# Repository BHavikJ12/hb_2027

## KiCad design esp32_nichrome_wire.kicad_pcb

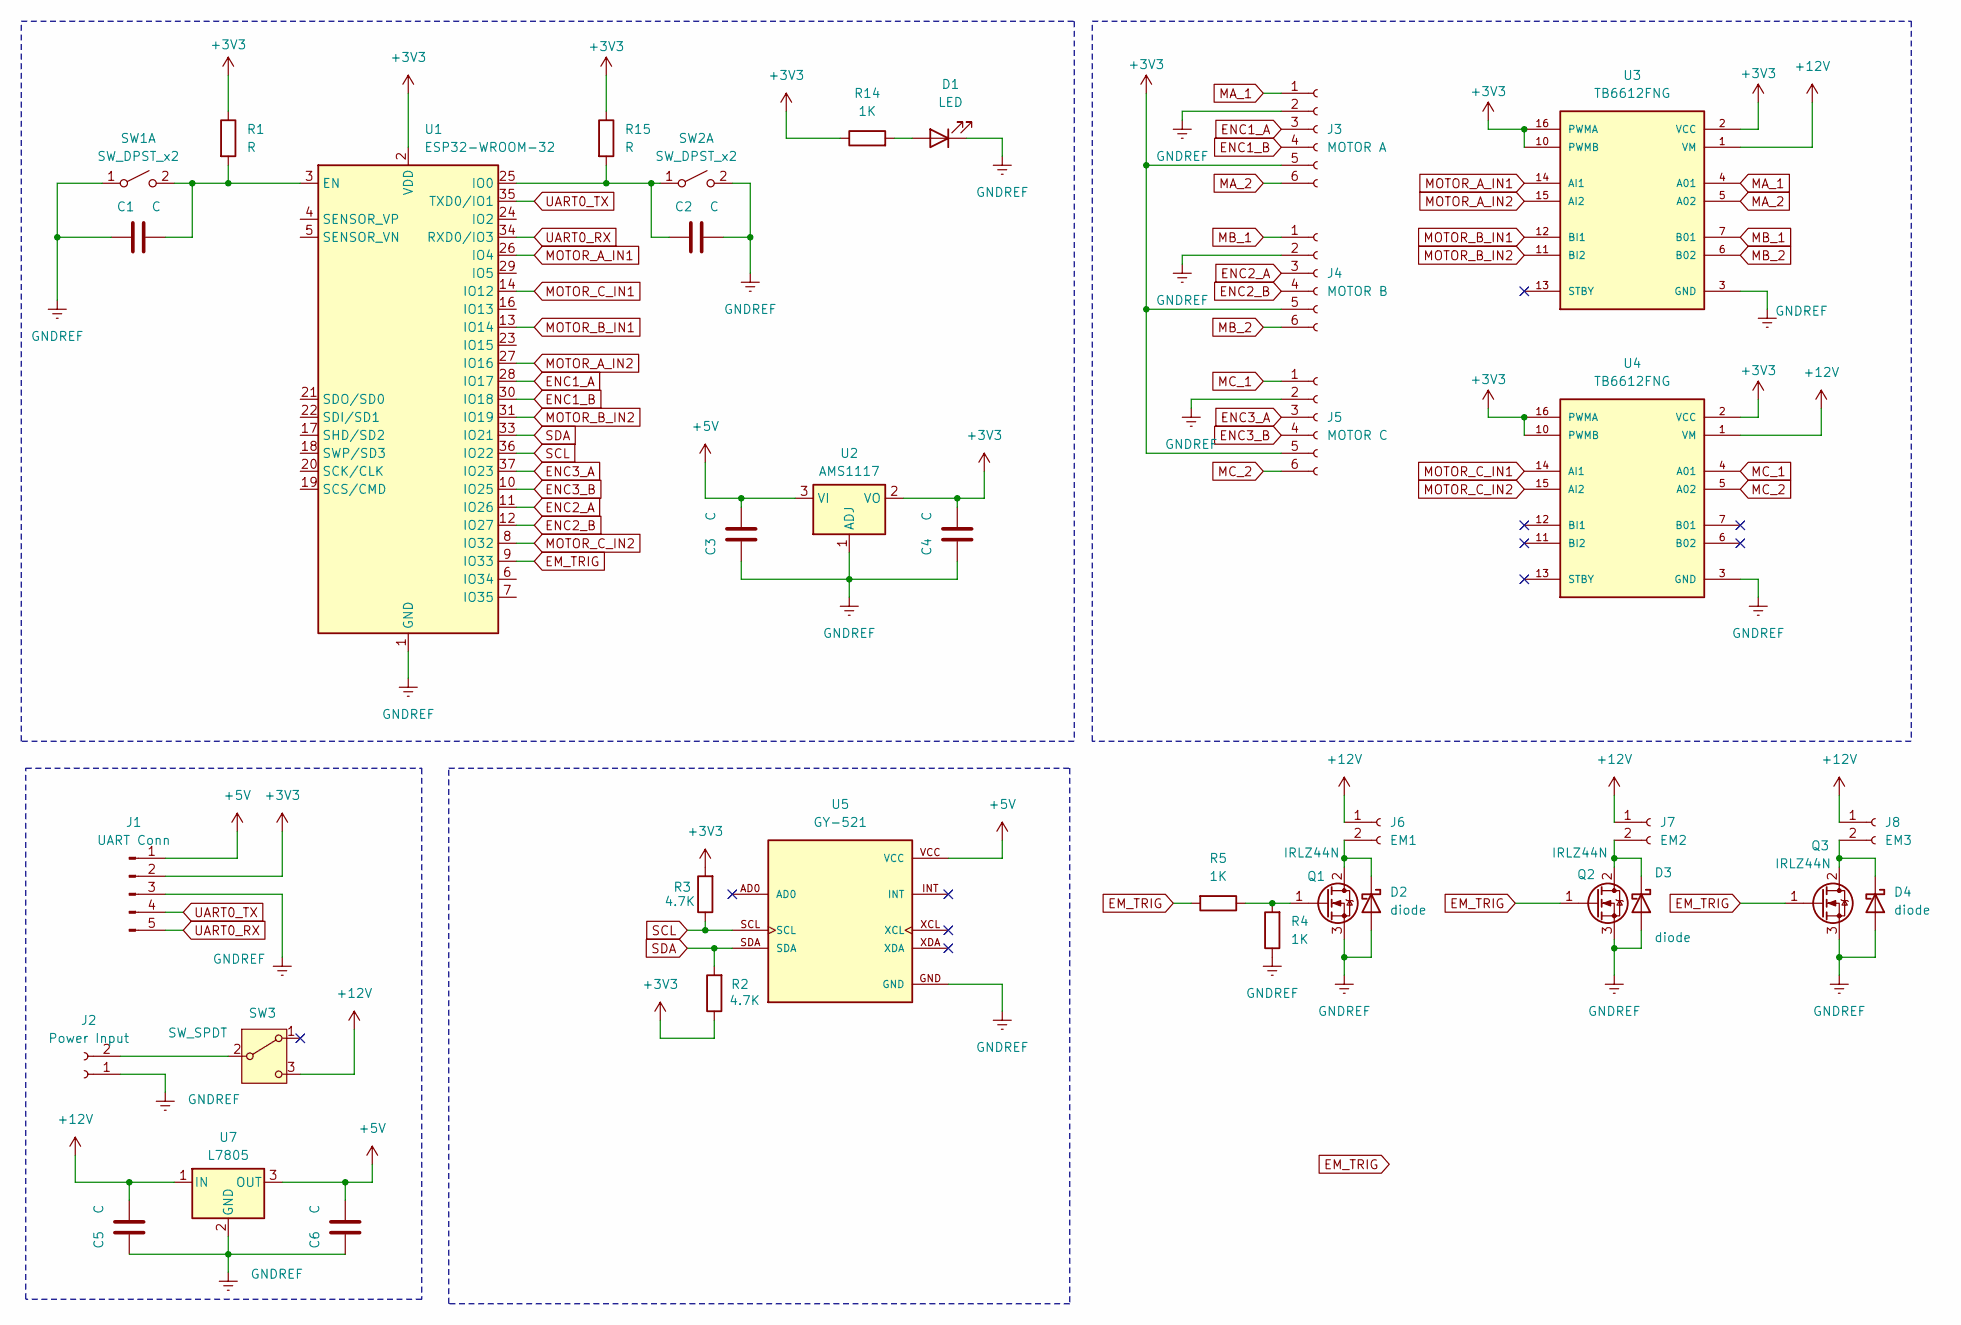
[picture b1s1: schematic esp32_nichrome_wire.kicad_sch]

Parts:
C1, C2, C3, C4, C5, C6: C; C_1206_3216Metric_Pad1.33x1.80mm_HandSolder
D1: LED; LED_1206_3216Metric
D2, D3, D4: diode; D_1206_3216Metric_Pad1.42x1.75mm_HandSolder
J1: UART Conn; PinHeader_1x05_P2.54mm_Vertical
J2: Power Input; AMASS_XT60-M_1x02_P7.20mm_Vertical
J3: MOTOR A; Wuerth_WR-WTB_64800611622_1x06_P1.50mm_Vertical
J4: MOTOR B; Wuerth_WR-WTB_64800611622_1x06_P1.50mm_Vertical
J5: MOTOR C; Wuerth_WR-WTB_64800611622_1x06_P1.50mm_Vertical
J6: EM1; PhoenixContact_MCV_1,5_2-G-3.5_1x02_P3.50mm_Vertical
J7: EM2; PhoenixContact_MCV_1,5_2-G-3.5_1x02_P3.50mm_Vertical
J8: EM3; PhoenixContact_MCV_1,5_2-G-3.5_1x02_P3.50mm_Vertical
Q1, Q2, Q3: IRLZ44N; TO-220-3_Vertical
R1, R15: R; R_1206_3216Metric
R2, R3: 4.7K; R_1206_3216Metric
R4, R5, R14: 1K; R_1206_3216Metric
SW1, SW2: SW_DPST_x2; SW_SPST_B3U-1000P
SW3: SW_SPDT; SW_100SP1T1B4M2QE
U1: ESP32-WROOM-32
U2: AMS1117; SOT-223-3_TabPin2
U3, U4: TB6612FNG; MODULE_ROB-14450; PARTREV 11-13-17
U5: GY-521; MODULE_GY-521; PARTREV NA
U7: L7805; TO-220-3_Vertical

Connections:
+3V3: C4.2, J1.2, J3.5, J4.5, J5.5, R1.1, R2.1, R3.2, R14.1, R15.1, U1.2 (VDD), U2.2 (VO), U3.2 (VCC), U3.10 (PWMB), U3.16 (PWMA), U4.2 (VCC), U4.10 (PWMB), U4.16 (PWMA)
+5V: C3.2, C6.2, J1.1, U2.3 (VI), U5.VCC, U7.3 (OUT)
+12V: C5.2, J6.1, J7.1, J8.1, SW3.3 (C), U3.1 (VM), U4.1 (VM), U7.1 (IN)
EM_TRIG: Q2.1 (G), Q3.1 (G), R5.2, U1.9 (IO33)
ENC1_A: J3.3, U1.28 (IO17)
ENC1_B: J3.4, U1.30 (IO18)
ENC2_A: J4.3, U1.11 (IO26)
ENC2_B: J4.4, U1.12 (IO27)
ENC3_A: J5.3, U1.37 (IO23)
ENC3_B: J5.4, U1.10 (IO25)
GNDREF: C1.1, C2.2, C3.1, C4.1, C5.1, C6.1, D1.1 (K), D2.2 (A), D3.2 (A), D4.2 (A), J1.3, J2.1, J3.2, J4.2, J5.2, Q1.3 (S), Q2.3 (S), Q3.3 (S), R4.1, SW1.1 (A), SW2.2 (B), U1.1 (GND), U1.15 (GND), U1.38 (GND), U1.39 (GND), U2.1 (ADJ), U3.3 (GND), U3.8 (GND), U3.9 (GND), U4.3 (GND), U4.8 (GND), U4.9 (GND), U5.GND, U7.2 (GND)
MA_1: J3.1, U3.4 (A01)
MA_2: J3.6, U3.5 (A02)
MB_1: J4.1, U3.7 (B01)
MB_2: J4.6, U3.6 (B02)
MC_1: J5.1, U4.4 (A01)
MC_2: J5.6, U4.5 (A02)
MOTOR_A_IN1: U1.26 (IO4), U3.14 (AI1)
MOTOR_A_IN2: U1.27 (IO16), U3.15 (AI2)
MOTOR_B_IN1: U1.13 (IO14), U3.12 (BI1)
MOTOR_B_IN2: U1.31 (IO19), U3.11 (BI2)
MOTOR_C_IN1: U1.14 (IO12), U4.14 (AI1)
MOTOR_C_IN2: U1.8 (IO32), U4.15 (AI2)
unnamed: D1.2 (A), R14.2
unnamed: D2.1 (K), J6.2, Q1.2 (D)
unnamed: D3.1 (K), J7.2, Q2.2 (D)
unnamed: D4.1 (K), J8.2, Q3.2 (D)
unnamed: J2.2, SW3.2 (B)
unnamed: Q1.1 (G), R4.2, R5.1
unnamed: C1.2, R1.2, SW1.2 (B), U1.3 (EN)
unnamed: C2.1, R15.2, SW2.1 (A), U1.25 (IO0)
SCL: R3.1, U1.36 (IO22), U5.SCL
SDA: R2.2, U1.33 (IO21), U5.SDA
UART0_RX: J1.5, U1.34 (RXD0/IO3)
UART0_TX: J1.4, U1.35 (TXD0/IO1)

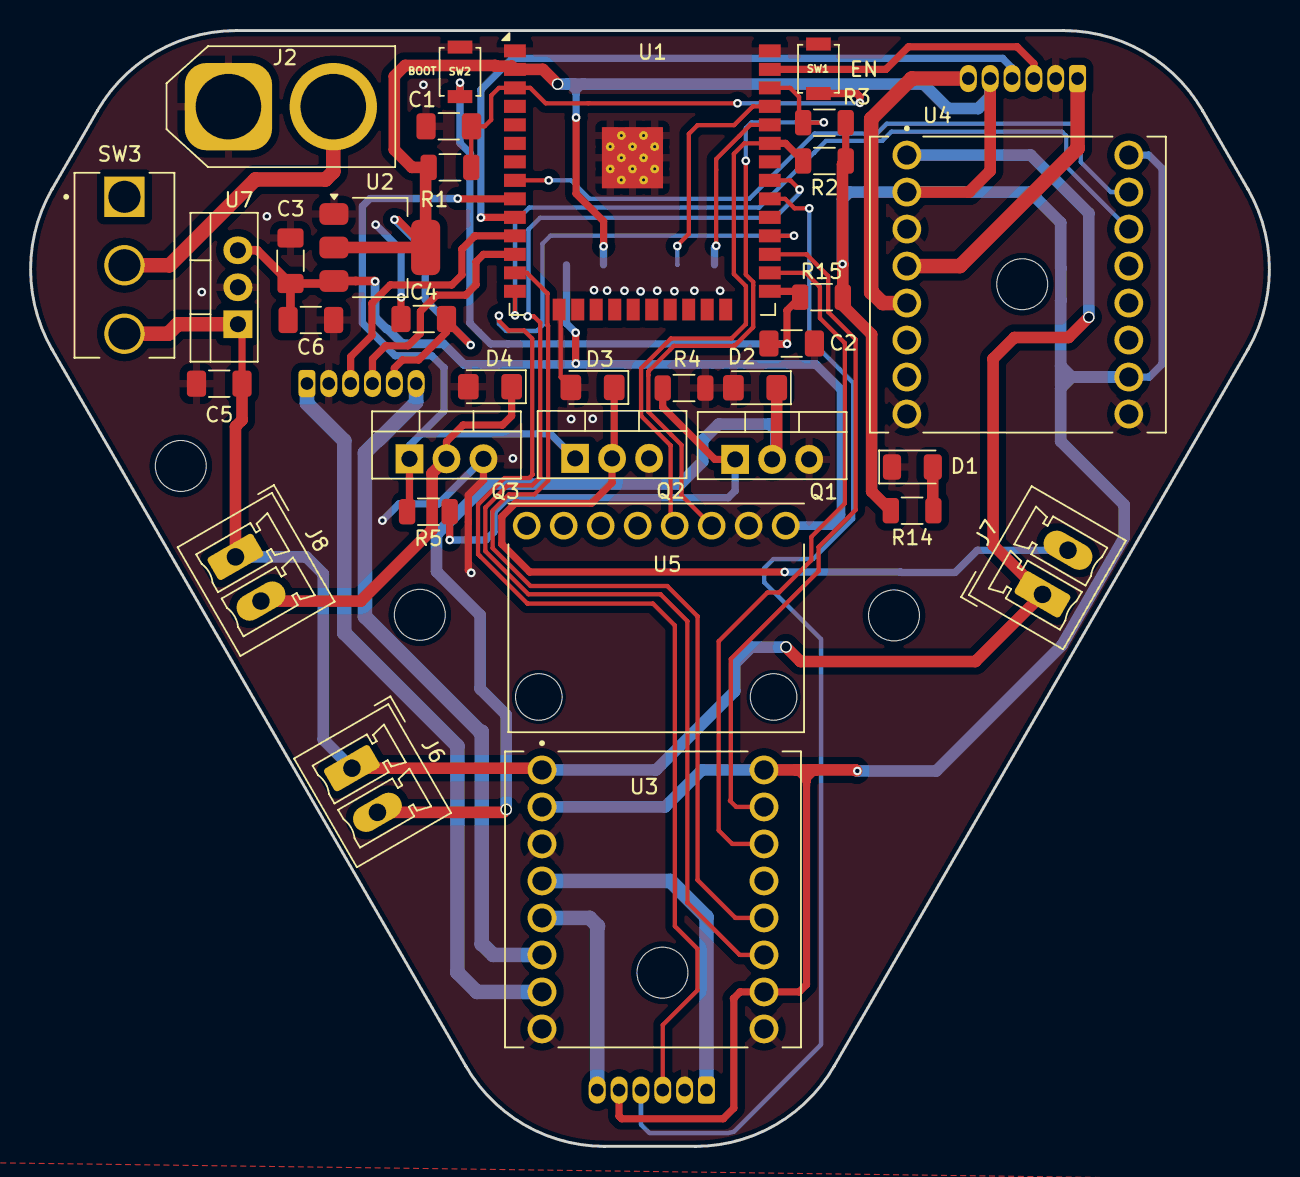
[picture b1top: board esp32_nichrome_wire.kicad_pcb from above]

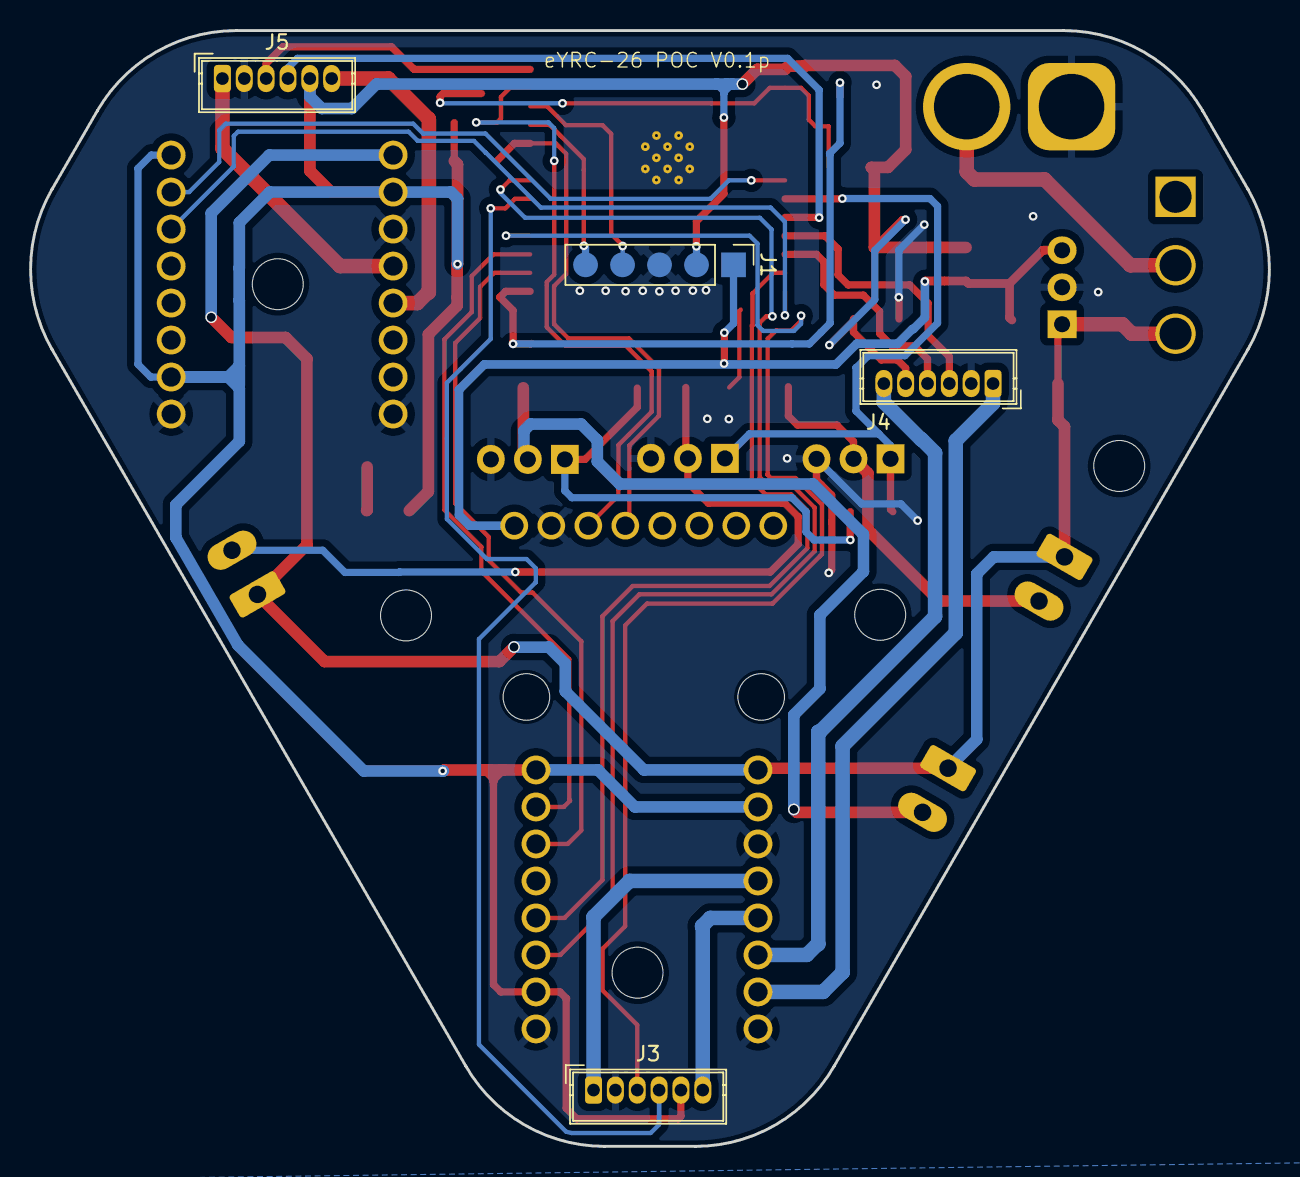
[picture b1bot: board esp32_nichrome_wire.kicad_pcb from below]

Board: 2 copper layers, 85.1 x 76.6 mm, 37 parts (4 on the bottom side), 35 nets.

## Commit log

2026-06-19 heheh Suiii
2026-06-19 Gerrrberrrr
